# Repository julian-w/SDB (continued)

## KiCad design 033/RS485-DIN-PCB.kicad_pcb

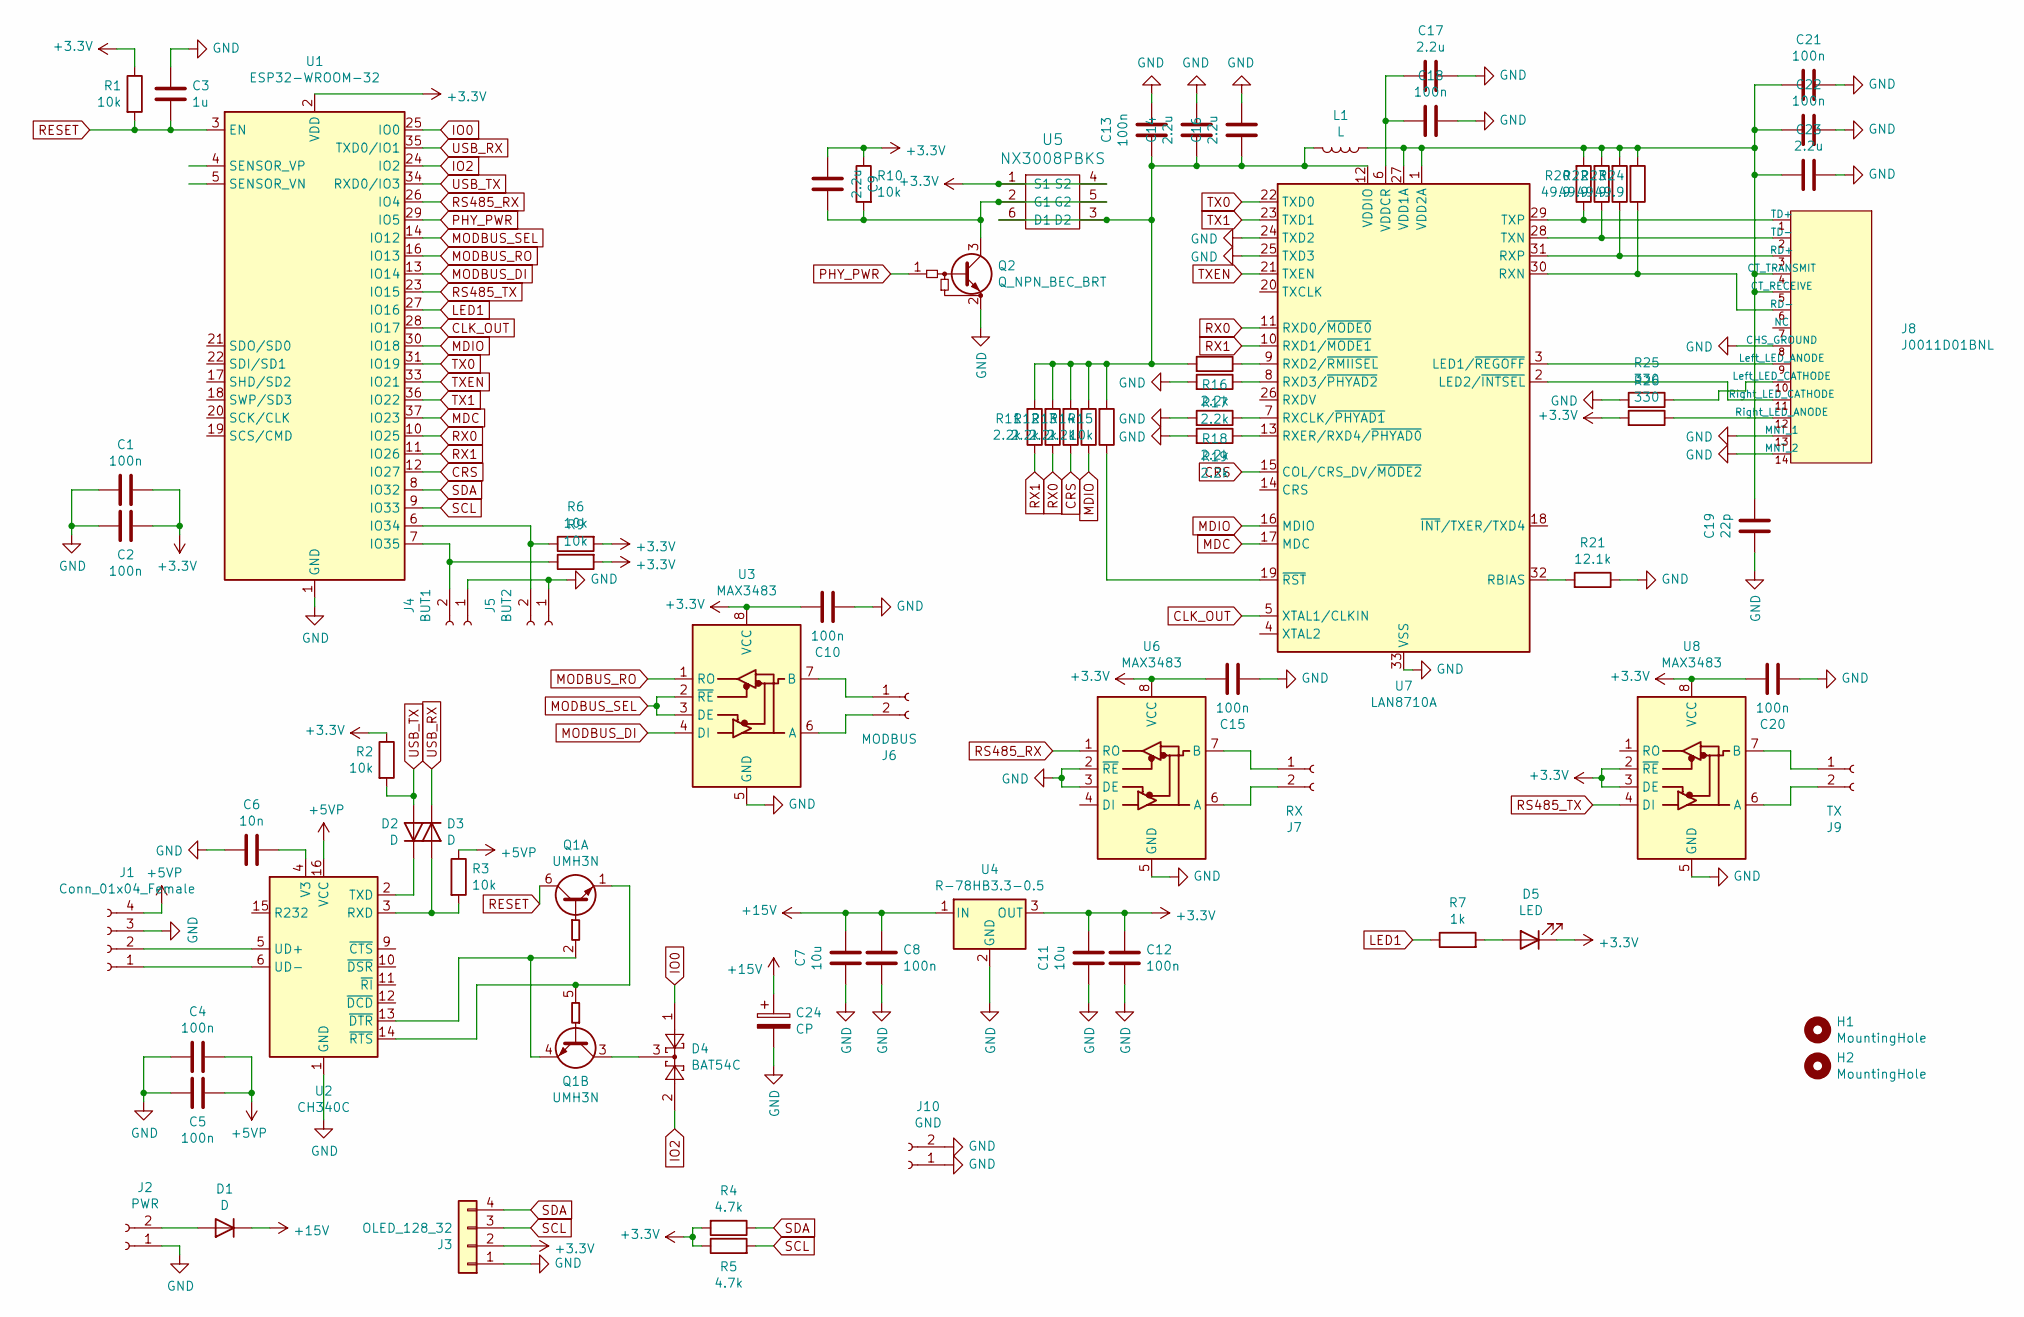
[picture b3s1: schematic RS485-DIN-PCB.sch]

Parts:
C1, C2, C4, C5, C10, C12, C13, C15, C18, C20, C21, C22: 100n; C_0603
C3: 1u; C_0603
C6: 10n; C_0603
C7: 10u; C_0805
C8: 100n; C_0805
C9, C14, C16, C17, C23: 2.2u; C_0603
C11: 10u; C_0603
C19: 22p; C_0603
C24: CP; CP_Radial_D8.0mm_P3.50mm
D1: D; D_SMA
D2, D3: D; D_SOD-123; LCSC C8598
D4: BAT54C; SOT-23
D5: LED; LED_D3.0mm_FlatTop
H1, H2: MountingHole; MountingHole_4.3mm_M4
J1: Conn_01x04_Female; PinHeader_1x04_P2.54mm_Vertical
J2: PWR; PinHeader_1x02_P2.54mm_Vertical
J3: OLED_128_32; SSD1306-0.91-OLED-4pin-128x32
J4: BUT1; PinHeader_1x02_P2.54mm_Vertical
J5: BUT2; PinHeader_1x02_P2.54mm_Vertical
J6: MODBUS; PinHeader_1x02_P2.54mm_Vertical
J7: RX; PinHeader_1x02_P2.54mm_Vertical
J8: J0011D01BNL; Pulse-J0011D01BNL-0-0-0; mouser part number 673-J0011D01BNL; digikey description CONN MAGJACK 1PORT 100 BASE-TX
J9: TX; PinHeader_1x02_P2.54mm_Vertical
J10: GND; PinHeader_1x02_P2.54mm_Vertical
L1: L; R_0603_HandSoldering
Q1: UMH3N; SOT-363_SC-70-6
Q2: Q_NPN_BEC_BRT; SOT-23
R1, R2, R3, R6, R9, R10, R15: 10k; R_0603
R4, R5: 4.7k; R_0603
R7: 1k; R_0603
R11, R12, R13, R14, R16, R17, R18, R19: 2.2k; R_0603
R20, R22, R23, R24: 49.9; R_0603
R21: 12.1k; R_0603
R25, R26: 330; R_0603
U1: ESP32-WROOM-32
U2: CH340C; SOIC-16_3.9x9.9mm_P1.27mm; LCSC C14267
U3, U6, U8: MAX3483; SOIC-8_3.9x4.9mm_P1.27mm
U4: R-78HB3.3-0.5; Converter_DCDC_RECOM_R-78HB-0.5_THT
U5: NX3008PBKS; TSOP-6_1.65x3.05mm_P0.95mm
U7: LAN8710A; QFN-32-1EP_5x5mm_P0.5mm_EP3.3x3.3mm_ThermalVias

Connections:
+3V3: C1.1, C2.1, C9.2, C10.1, C11.1, C12.1, C15.1, C20.1, D5.1 (K), J3.2, R1.1, R2.1, R4.2, R5.1, R6.2, R9.2, R10.1, R26.2, U1.2 (VDD), U3.8 (VCC), U4.3 (OUT), U5.1 (S1), U5.4 (S2), U6.8 (VCC), U8.2 (~RE), U8.3 (DE), U8.8 (VCC)
+5VP: C4.1, C5.1, J1.4, R3.1, U2.16 (VCC)
+15V: C7.1, C8.1, C24.1, D1.1 (K), U4.1 (IN)
CLK_OUT: U1.28 (IO17), U7.5 (XTAL1/CLKIN)
CRS: R13.1, U1.12 (IO27), U7.15 (COL/CRS_DV/~MODE2)
GND: C1.2, C2.2, C3.2, C4.2, C5.2, C6.2, C7.2, C8.2, C10.2, C11.2, C12.2, C13.1, C14.1, C15.2, C16.1, C17.1, C18.1, C19.2, C20.2, C21.1, C22.1, C23.1, C24.2, J1.3, J2.1, J3.1, J4.1, J5.1, J8.8 (CHS_GROUND), J8.13 (MNT_1), J8.14 (MNT_2), J10.1, J10.2, Q2.2 (E), R17.2, R18.2, R19.2, R21.1, R25.2, U1.1 (GND), U1.15 (GND), U1.38 (GND), U1.39 (GND), U2.1 (GND), U3.5 (GND), U4.2 (GND), U6.2 (~RE), U6.3 (DE), U6.5 (GND), U7.24 (TXD2), U7.25 (TXD3), U7.33 (VSS), U8.5 (GND)
IO0: D4.1, U1.25 (IO0)
IO2: D4.2, U1.24 (IO2)
LED1: R7.1, U1.27 (IO16)
MDC: U1.37 (IO23), U7.17 (MDC)
MDIO: R14.1, U1.30 (IO18), U7.16 (MDIO)
MODBUS_DI: U1.13 (IO14), U3.4 (DI)
MODBUS_RO: U1.16 (IO13), U3.1 (RO)
MODBUS_SEL: U1.14 (IO12), U3.2 (~RE), U3.3 (DE)
unnamed: C6.1, U2.4 (V3)
unnamed: C9.1, Q2.3 (C), R10.2, U5.2 (G1), U5.5 (G2)
unnamed: C13.2, C14.2, C16.2, L1.2, R11.2, R12.2, R13.2, R14.2, R15.2, R16.2, U5.3 (D2), U5.6 (D1), U7.12 (VDDIO)
unnamed: C17.2, C18.2, U7.6 (VDDCR)
unnamed: C19.1, C21.2, C22.2, C23.2, J8.4 (CT_TRANSMIT), J8.5 (CT_RECEIVE), L1.1, R20.2, R22.2, R23.2, R24.2, U7.1 (VDD2A), U7.27 (VDD1A)
unnamed: D1.2 (A), J2.2
unnamed: D2.1 (K), U2.2 (TXD)
unnamed: D3.2 (A), R3.2, U2.3 (RXD)
unnamed: D4.3, Q1.3 (C2)
unnamed: D5.2 (A), R7.2
unnamed: J1.1, U2.6 (UD-)
unnamed: J1.2, U2.5 (UD+)
unnamed: J4.2, R9.1, U1.7 (IO35)
unnamed: J5.2, R6.1, U1.6 (IO34)
unnamed: J6.1, U3.7 (B)
unnamed: J6.2, U3.6 (A)
unnamed: J7.1, U6.7 (B)
unnamed: J7.2, U6.6 (A)
unnamed: J8.1 (TD+), R20.1, U7.29 (TXP)
unnamed: J8.2 (TD-), R22.1, U7.28 (TXN)
unnamed: J8.3 (RD+), R23.1, U7.31 (RXP)
unnamed: J8.6 (RD-), R24.1, U7.30 (RXN)
unnamed: J8.9 (Left_LED_ANODE), U7.3 (LED1/~REGOFF)
unnamed: J8.10 (Left_LED_CATHODE), R25.1
unnamed: J8.11 (Right_LED_CATHODE), U7.2 (LED2/~INTSEL)
unnamed: J8.12 (Right_LED_ANODE), R26.1
unnamed: J9.1, U8.7 (B)
unnamed: J9.2, U8.6 (A)
unnamed: Q1.1 (E1), Q1.5 (B2), U2.14 (~RTS)
unnamed: Q1.2 (B1), Q1.4 (E2), U2.13 (~DTR)
unnamed: R15.1, U7.19 (~RST)
unnamed: R16.1, U7.9 (RXD2/~RMIISEL)
unnamed: R17.1, U7.8 (RXD3/~PHYAD2)
unnamed: R18.1, U7.7 (RXCLK/~PHYAD1)
unnamed: R19.1, U7.13 (RXER/RXD4/~PHYAD0)
unnamed: R21.2, U7.32 (RBIAS)
PHY_PWR: Q2.1 (B), U1.29 (IO5)
RESET: C3.1, Q1.6 (C1), R1.2, U1.3 (EN)
RS485_RX: U1.26 (IO4), U6.1 (RO)
RS485_TX: U1.23 (IO15), U8.4 (DI)
RX0: R12.1, U1.10 (IO25), U7.11 (RXD0/~MODE0)
RX1: R11.1, U1.11 (IO26), U7.10 (RXD1/~MODE1)
SCL: J3.3, R5.2, U1.9 (IO33)
SDA: J3.4, R4.1, U1.8 (IO32)
TX0: U1.31 (IO19), U7.22 (TXD0)
TX1: U1.36 (IO22), U7.23 (TXD1)
TXEN: U1.33 (IO21), U7.21 (TXEN)
USB_RX: D3.1 (K), U1.35 (TXD0/IO1)
USB_TX: D2.2 (A), R2.2, U1.34 (RXD0/IO3)

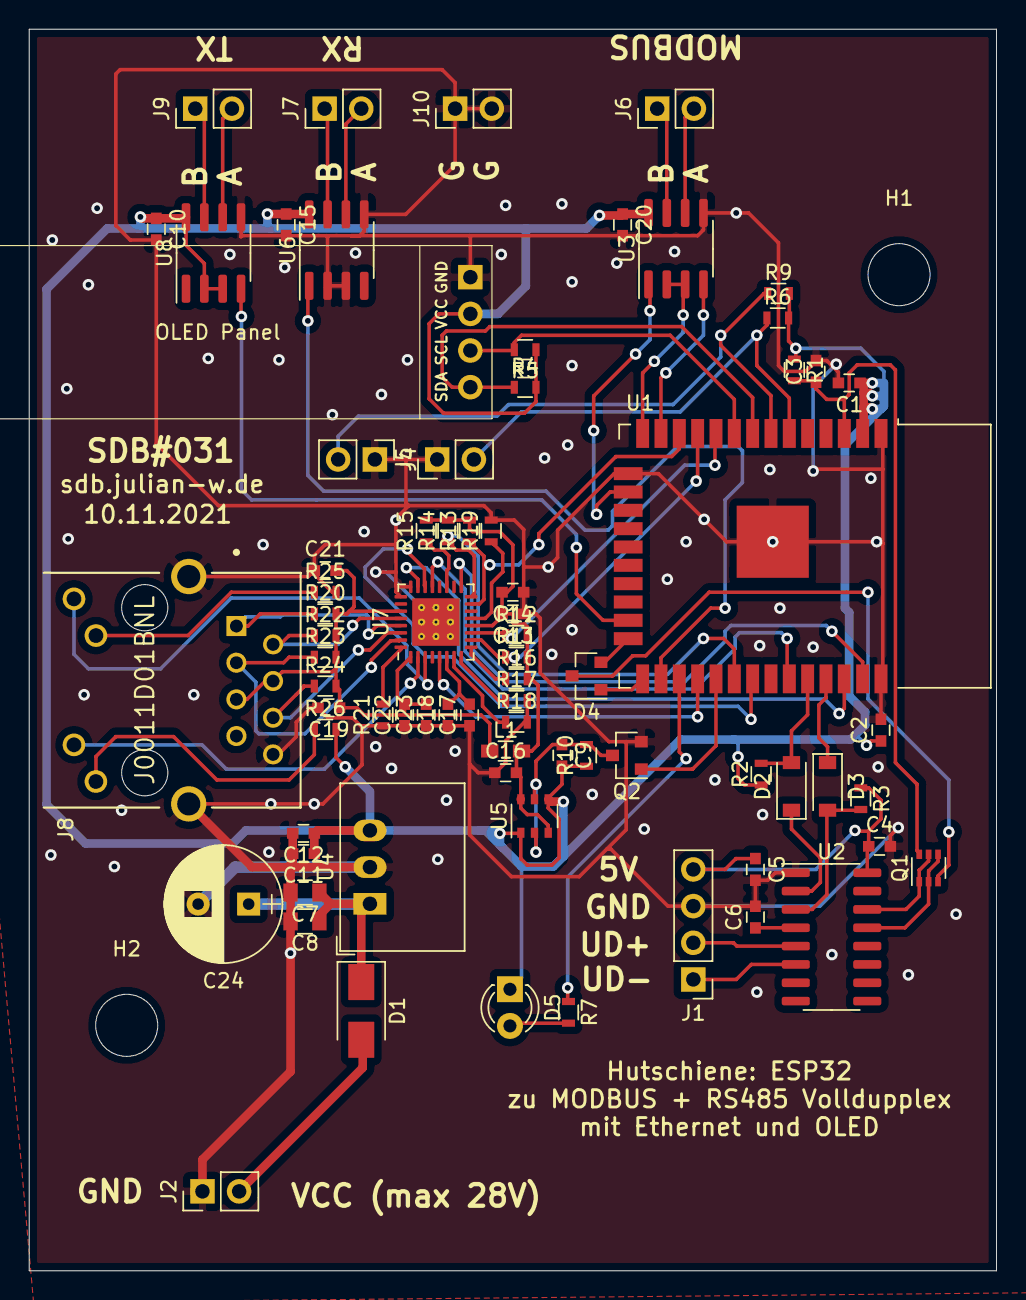
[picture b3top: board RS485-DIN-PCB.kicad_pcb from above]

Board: 2 copper layers, 67.0 x 86.0 mm, 77 parts (0 on the bottom side), 63 nets.

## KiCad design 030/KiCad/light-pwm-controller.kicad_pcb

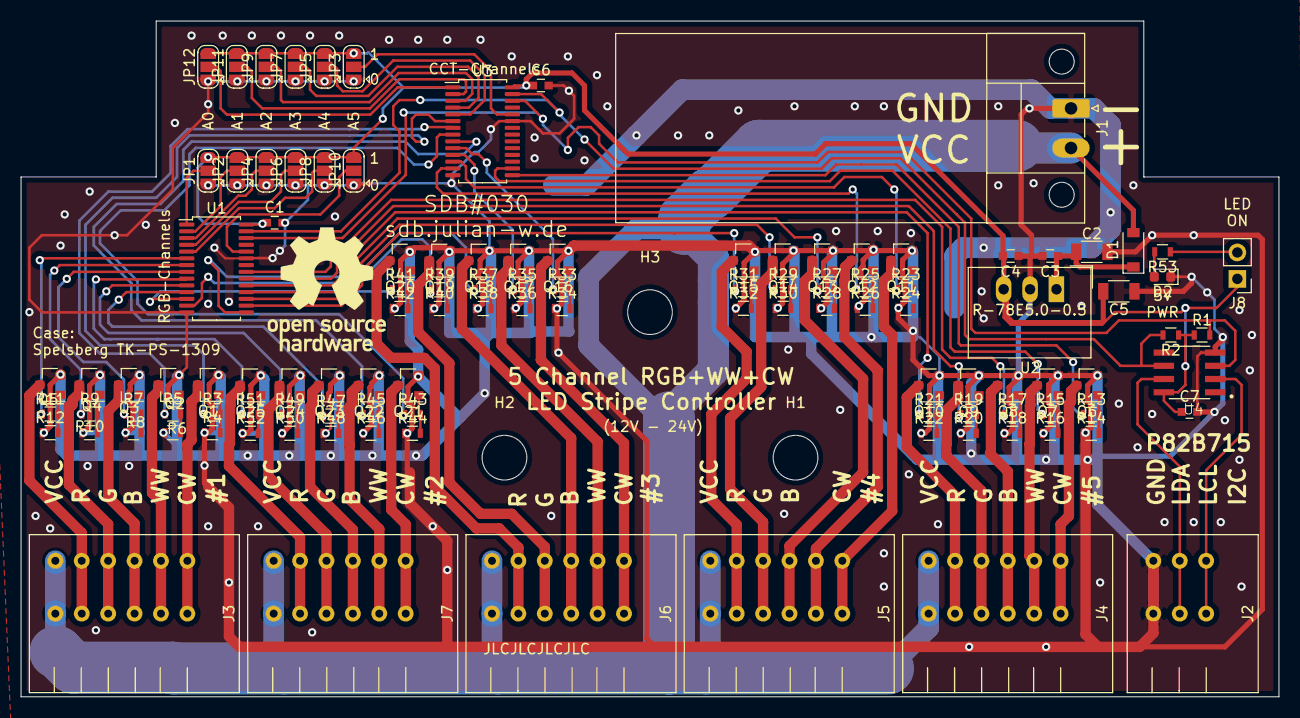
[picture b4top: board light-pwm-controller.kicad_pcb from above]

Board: 2 copper layers, 121.0 x 65.0 mm, 115 parts (0 on the bottom side), 97 nets.

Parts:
C1, C3, C4, C6, C7: 100n; C_0603
C2, C5: 10u; C_1206
D1: D; D_SOD-123
D2: LED; LED_0603_1608Metric
H1, H2, H3: MountingHole; MountingHole_4.3mm_M4
J1: Conn_01x02; PhoenixContact_MC_1,5_2-GF-3.81_1x02_P3.81mm_Horizontal_Thr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
J2: Conn_01x03; 3x2.54SpringClamp
J3, J4, J5, J6, J7: Conn_01x06; 6x2.54SpringClamp
J8: Conn_01x02; PinHeader_1x02_P2.54mm_Vertical
JP1, JP12: 1A0; SolderJumper-3_P1.3mm_Open_RoundedPad1.0x1.5mm
JP2, JP11: 1A1; SolderJumper-3_P1.3mm_Open_RoundedPad1.0x1.5mm
JP3, JP10: 1A5; SolderJumper-3_P1.3mm_Open_RoundedPad1.0x1.5mm
JP4, JP9: 1A2; SolderJumper-3_P1.3mm_Open_RoundedPad1.0x1.5mm
JP5, JP8: 1A4; SolderJumper-3_P1.3mm_Open_RoundedPad1.0x1.5mm
JP6, JP7: 1A3; SolderJumper-3_P1.3mm_Open_RoundedPad1.0x1.5mm
LOGO1: OSHW-LOGOM; OSHW-Logo_11.4x12mm_SilkScreen
Q1, Q2, Q3, Q4, Q5, Q6, Q7, Q8, Q9, Q10, Q11, Q12, Q13, Q14, Q15, Q16, Q17, Q18, Q19, Q20, Q21, Q22, Q23, Q24, Q25: IRLML6344; SOT-23
R1, R2: 4.7k; R_0603
R3, R5, R7, R9, R11, R13, R15, R17, R19, R21, R23, R25, R27, R29, R31, R33, R35, R37, R39, R41, R43, R45, R47, R49, R51: 100; R_0603
R4, R6, R8, R10, R12, R14, R16, R18, R20, R22, R24, R26, R28, R30, R32, R34, R36, R38, R40, R42, R44, R46, R48, R50, R52: 10k; R_0603
R53: 1k; R_0603
U1, U3: PCA9685PW; TSSOP-28_4.4x9.7mm_P0.65mm
U2: R-78E5.0-0.5; DCDC-Conv_RECOM_R-78E-0.5
U4: P82B715DR; SOIC127P599X175-8N

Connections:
+5V: C1.1, C4.2, C5.2, C6.1, C7.1, J8.1, JP1.3, JP2.3, JP3.3, JP4.3, JP5.3, JP6.3, JP7.3, JP8.3, JP9.3, JP10.3, JP11.3, JP12.3, R1.1, R2.1, U1.28, U2.3, U3.28, U4.8
+12V: D1.2, J1.2, J3.6, J4.6, J5.6, J6.6, J7.6
/output-stage-1/B: R7.1, U1.8
/output-stage-1/CW: R3.1, U3.6
/output-stage-1/G: R9.1, U1.7
/output-stage-1/R: R11.1, U1.6
/output-stage-1/WW: R5.1, U3.7
/output-stage-2/B: R17.1, U1.21
/output-stage-2/CW: R13.1, U3.15
/output-stage-2/G: R19.1, U1.20
/output-stage-2/R: R21.1, U1.19
/output-stage-2/WW: R15.1, U3.16
/output-stage-3/B: R27.1, U1.18
/output-stage-3/CW: R23.1, U3.12
/output-stage-3/G: R29.1, U1.17
/output-stage-3/R: R31.1, U1.16
/output-stage-3/WW: R25.1, U3.13
/output-stage-4/B: R37.1, U1.15
/output-stage-4/CW: R33.1, U3.10
/output-stage-4/G: R39.1, U1.13
/output-stage-4/R: R41.1, U1.12
/output-stage-4/WW: R35.1, U3.11
/output-stage-5/B: R47.1, U1.11
/output-stage-5/CW: R43.1, U3.8
/output-stage-5/G: R49.1, U1.10
/output-stage-5/R: R51.1, U1.9
/output-stage-5/WW: R45.1, U3.9
GND: C1.2, C2.2, C3.2, C4.1, C5.1, C6.2, C7.2, D2.1, J1.1, J2.3, JP1.1, JP2.1, JP3.1, JP4.1, JP5.1, JP6.1, JP7.1, JP8.1, JP9.1, JP10.1, JP11.1, JP12.1, Q1.2, Q2.2, Q3.2, Q4.2, Q5.2, Q6.2, Q7.2, Q8.2, Q9.2, Q10.2, Q11.2, Q12.2, Q13.2, Q14.2, Q15.2, Q16.2, Q17.2, Q18.2, Q19.2, Q20.2, Q21.2, Q22.2, Q23.2, Q24.2, Q25.2, R4.1, R6.1, R8.1, R10.1, R12.1, R14.1, R16.1, R18.1, R20.1, R22.1, R24.1, R26.1, R28.1, R30.1, R32.1, R34.1, R36.1, R38.1, R40.1, R42.1, R44.1, R46.1, R48.1, R50.1, R52.1, U1.14, U1.23, U2.2, U3.14, U3.23, U4.4
unnamed: C2.1, C3.1, D1.1, U2.1
unnamed: D2.2, R53.2
unnamed: J2.1, U4.2
unnamed: J2.2, U4.7
unnamed: J3.1, Q1.3
unnamed: J3.2, Q2.3
unnamed: J3.3, Q3.3
unnamed: J3.4, Q4.3
unnamed: J3.5, Q5.3
unnamed: J4.1, Q6.3
unnamed: J4.2, Q7.3
unnamed: J4.3, Q8.3
unnamed: J4.4, Q9.3
unnamed: J4.5, Q10.3
unnamed: J5.1, Q11.3
unnamed: J5.2, Q12.3
unnamed: J5.3, Q13.3
unnamed: J5.4, Q14.3
unnamed: J5.5, Q15.3
unnamed: J6.1, Q16.3
unnamed: J6.2, Q17.3
unnamed: J6.3, Q18.3
unnamed: J6.4, Q19.3
unnamed: J6.5, Q20.3
unnamed: J7.1, Q21.3
unnamed: J7.2, Q22.3
unnamed: J7.3, Q23.3
unnamed: J7.4, Q24.3
unnamed: J7.5, Q25.3
unnamed: J8.2, R53.1
unnamed: JP1.2, U1.1
unnamed: JP2.2, U1.2
unnamed: JP3.2, U3.24
unnamed: JP4.2, U1.3
unnamed: JP5.2, U3.5
unnamed: JP6.2, U1.4
unnamed: JP7.2, U3.4
unnamed: JP8.2, U1.5
unnamed: JP9.2, U3.3
unnamed: JP10.2, U1.24
unnamed: JP11.2, U3.2
unnamed: JP12.2, U3.1
unnamed: Q1.1, R3.2, R4.2
unnamed: Q2.1, R5.2, R6.2
unnamed: Q3.1, R7.2, R8.2
unnamed: Q4.1, R9.2, R10.2
unnamed: Q5.1, R11.2, R12.2
unnamed: Q6.1, R13.2, R14.2
unnamed: Q7.1, R15.2, R16.2
unnamed: Q8.1, R17.2, R18.2
unnamed: Q9.1, R19.2, R20.2
unnamed: Q10.1, R21.2, R22.2
unnamed: Q11.1, R23.2, R24.2
unnamed: Q12.1, R25.2, R26.2
unnamed: Q13.1, R27.2, R28.2
unnamed: Q14.1, R29.2, R30.2
unnamed: Q15.1, R31.2, R32.2
unnamed: Q16.1, R33.2, R34.2
unnamed: Q17.1, R35.2, R36.2
unnamed: Q18.1, R37.2, R38.2
unnamed: Q19.1, R39.2, R40.2
unnamed: Q20.1, R41.2, R42.2
unnamed: Q21.1, R43.2, R44.2
unnamed: Q22.1, R45.2, R46.2
unnamed: Q23.1, R47.2, R48.2
unnamed: Q24.1, R49.2, R50.2
unnamed: Q25.1, R51.2, R52.2
SCL: R1.2, U1.26, U3.26, U4.3
SDA: R2.2, U1.27, U3.27, U4.6

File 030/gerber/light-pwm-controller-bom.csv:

Comment,Designator,Footprint,LCSC
10u,"C2,C5",Capacitors_SMD:C_1206,C13585
100n,"C1,C3,C4,C6,C7",Capacitors_SMD:C_0603,C14663
D,D1,Diodes_SMD:D_SOD-123,C8598
LED,D2,LED_SMD:LED_0603_1608Metric,C2286
MountingHole,"H1,H2,H3",Mounting_Holes:MountingHole_4.3mm_M4,
Conn_01x02,J1,"Connector_Phoenix_MC:PhoenixContact_MC_1,5_2-GF-3.81_1x02_P3.81mm_Horizontal_ThreadedFlange_MountHole",
Conn_01x03,J2,P-250-402:3x2.54SpringClamp,
Conn_01x06,"J3,J4,J5,J6,J7",P-250-402:6x2.54SpringClamp,
Conn_01x02,J8,Connector_PinHeader_2.54mm:PinHeader_1x02_P2.54mm_Vertical,
1A0,"JP1,JP12",SolderJumper:SolderJumper-3_P1.3mm_Open_RoundedPad1.0x1.5mm,
1A5,"JP3,JP10",SolderJumper:SolderJumper-3_P1.3mm_Open_RoundedPad1.0x1.5mm,
1A1,"JP2,JP11",SolderJumper:SolderJumper-3_P1.3mm_Open_RoundedPad1.0x1.5mm,
1A2,"JP4,JP9",SolderJumper:SolderJumper-3_P1.3mm_Open_RoundedPad1.0x1.5mm,
1A3,"JP6,JP7",SolderJumper:SolderJumper-3_P1.3mm_Open_RoundedPad1.0x1.5mm,
1A4,"JP5,JP8",SolderJumper:SolderJumper-3_P1.3mm_Open_RoundedPad1.0x1.5mm,
OSHW-LOGOM,LOGO1,Symbols:OSHW-Logo_11.4x12mm_SilkScreen,
IRLML6344,"Q1,Q2,Q3,Q4,Q5,Q6,Q7,Q8,Q9,Q10,Q11,Q12,Q13,Q14,Q15,Q16,Q17,Q18,Q19,Q20,Q21,Q22,Q23,Q24,Q25",Package_TO_SOT_SMD:SOT-23,C53550
4.7k,"R1,R2",Resistors_SMD:R_0603,C23162
100,"R3,R5,R7,R9,R11,R13,R15,R17,R19,R21,R23,R25,R27,R29,R31,R33,R35,R37,R39,R41,R43,R45,R47,R49,R51",Resistors_SMD:R_0603,C22775
1k,R53,Resistors_SMD:R_0603,C21190
10k,"R4,R6,R8,R10,R12,R14,R16,R18,R20,R22,R24,R26,R28,R30,R32,R34,R36,R38,R40,R42,R44,R46,R48,R50,R52",Resistors_SMD:R_0603,C25804
PCA9685PW,"U1,U3",Package_SO:TSSOP-28_4.4x9.7mm_P0.65mm,
R-78E5.0-0.5,U2,Converters_DCDC_ACDC:DCDC-Conv_RECOM_R-78E-0.5,
P82B715DR,U4,footprints:SOIC127P599X175-8N,

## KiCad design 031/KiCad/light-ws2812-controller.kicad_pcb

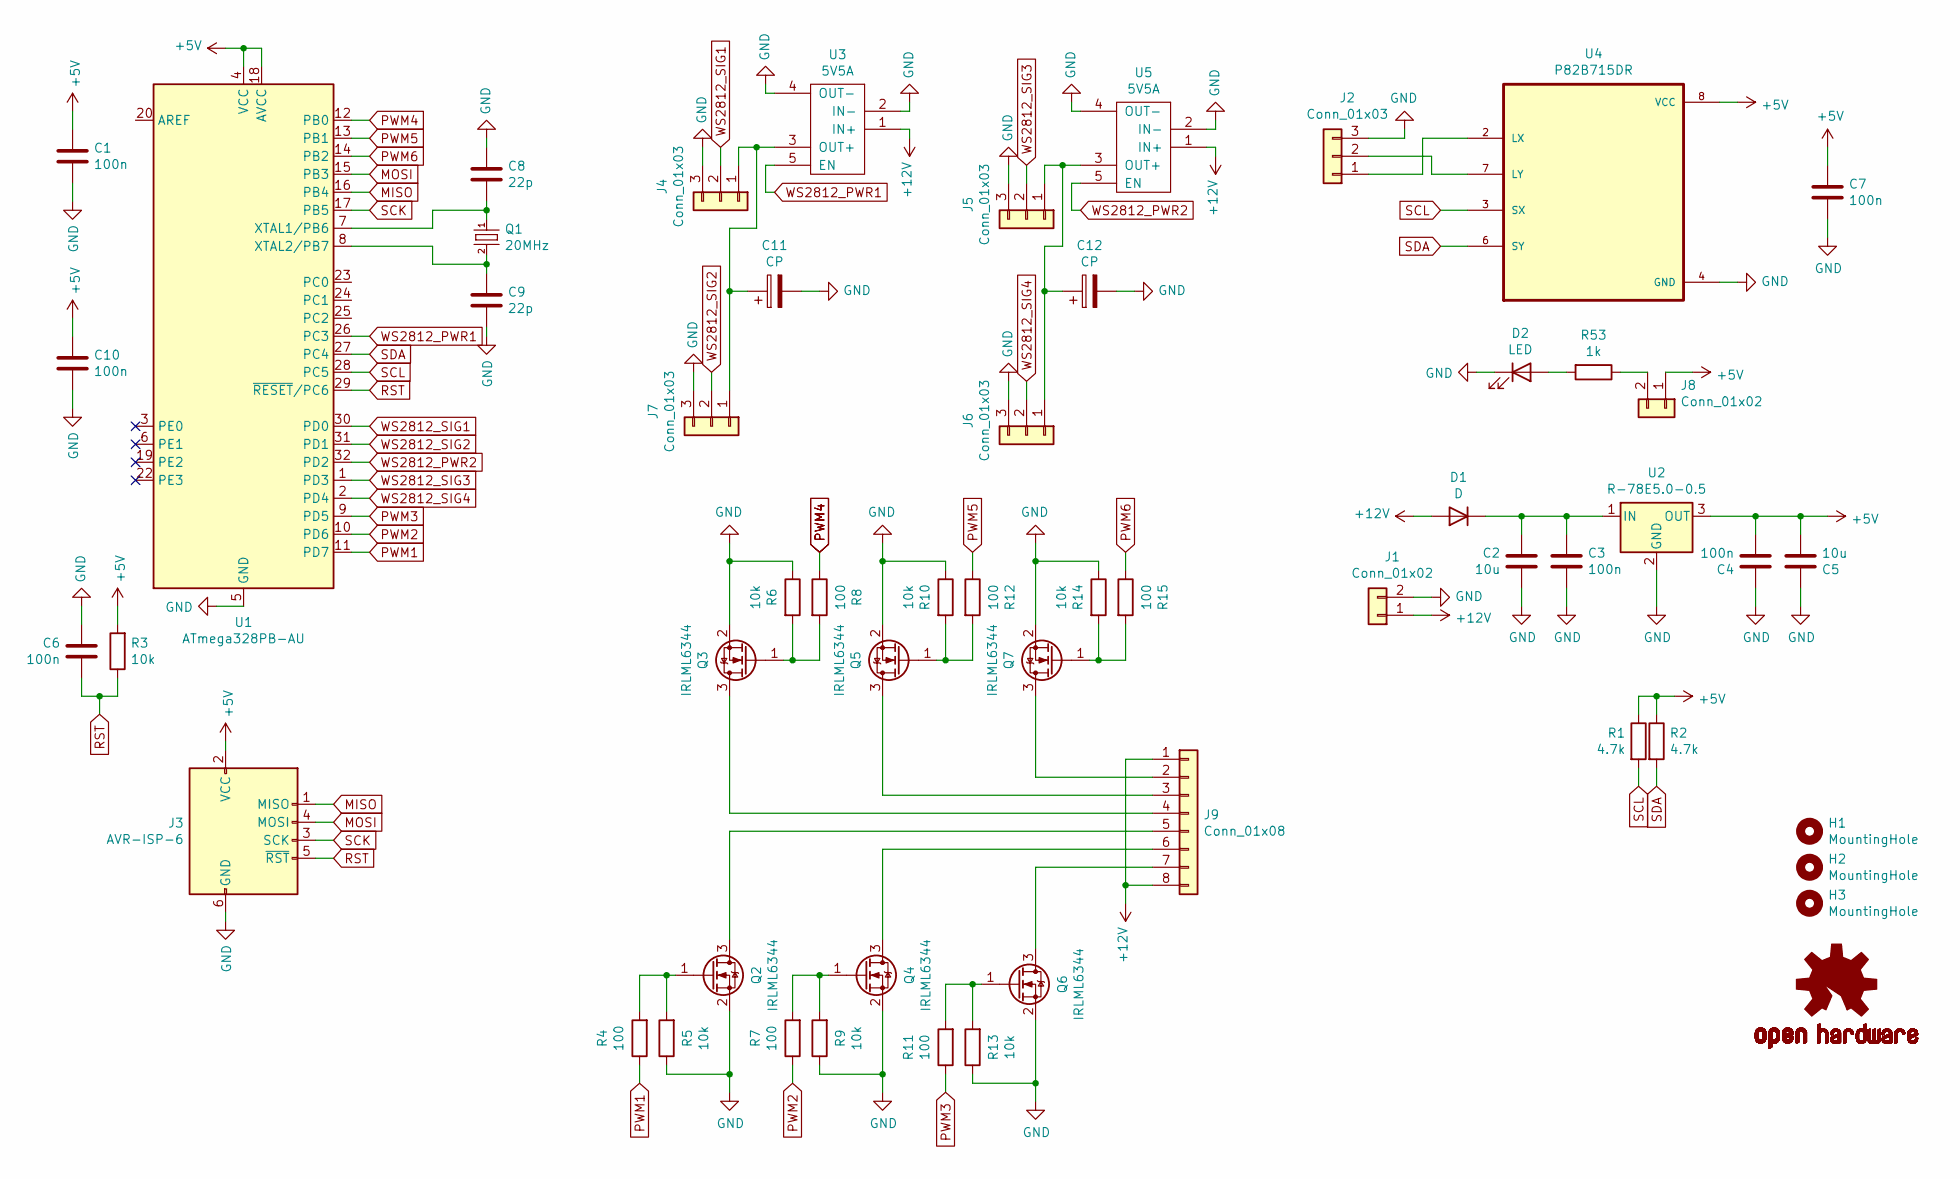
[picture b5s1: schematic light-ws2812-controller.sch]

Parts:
C1, C3, C4, C6, C7, C10: 100n; C_0603_HandSoldering
C2, C5: 10u; C_1206_HandSoldering
C8, C9: 22p; C_0603_HandSoldering
C11, C12: CP; CP_Radial_D10.0mm_P5.00mm_P7.50mm
D1: D; D_SOD-123
D2: LED; LED_0603_1608Metric
H1, H2, H3: MountingHole; MountingHole_4.3mm_M4
J1: Conn_01x02; PhoenixContact_MC_1,5_2-GF-3.81_1x02_P3.81mm_Horizontal_Thr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
J2, J4, J5, J6, J7: Conn_01x03; 3x2.54SpringClamp
J3: AVR-ISP-6; IDC-Header_2x03_P2.54mm_Vertical
J8: Conn_01x02; PinHeader_1x02_P2.54mm_Vertical
J9: Conn_01x08; 8x2.54SpringClamp
LOGO1: OSHW-LOGOM; OSHW-Logo_11.4x12mm_SilkScreen
Q1: 20MHz; Crystal_HC49-4H_Vertical
Q2, Q3, Q4, Q5, Q6, Q7: IRLML6344; SOT-23; LCSC C53550
R1, R2: 4.7k; R_0603_HandSoldering
R3, R5, R6, R9, R10, R13, R14: 10k; R_0603_HandSoldering
R4, R7, R8, R11, R12, R15: 100; R_0603_HandSoldering
R53: 1k; R_0603_HandSoldering
U1: ATmega328PB-AU; TQFP-32_7x7mm_P0.8mm
U2: R-78E5.0-0.5; DCDC-Conv_RECOM_R-78E-0.5
U3, U5: 5V5A
U4: P82B715DR; SOIC127P599X175-8N

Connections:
+5V: C1.1, C4.2, C5.2, C7.1, C10.1, J3.2 (VCC), J8.1, R1.1, R2.1, R3.2, U1.4 (VCC), U1.18 (AVCC), U2.3 (OUT), U4.8 (VCC)
+12V: D1.2 (A), J1.1, J9.1, J9.8, U3.1 (IN+), U5.1 (IN+)
GND: C1.2, C2.2, C3.2, C4.1, C5.1, C6.2, C7.2, C8.1, C9.2, C10.2, C11.2, C12.2, D2.1 (K), J1.2, J2.3, J3.6 (GND), J4.3, J5.3, J6.3, J7.3, Q2.2 (S), Q3.2 (S), Q4.2 (S), Q5.2 (S), Q6.2 (S), Q7.2 (S), R5.1, R6.1, R9.1, R10.1, R13.1, R14.1, U1.5 (GND), U1.21 (GND), U2.2 (GND), U3.2 (IN-), U3.4 (OUT-), U4.4 (GND), U5.2 (IN-), U5.4 (OUT-)
MISO: J3.1 (MISO), U1.16 (PB4)
MOSI: J3.4 (MOSI), U1.15 (PB3)
unnamed: C2.1, C3.1, D1.1 (K), U2.1 (IN)
unnamed: C8.2, Q1.1, U1.7 (XTAL1/PB6)
unnamed: C9.1, Q1.2, U1.8 (XTAL2/PB7)
unnamed: C11.1, J4.1, J7.1, U3.3 (OUT+)
unnamed: C12.1, J5.1, J6.1, U5.3 (OUT+)
unnamed: D2.2 (A), R53.2
unnamed: J2.1, U4.2 (LX)
unnamed: J2.2, U4.7 (LY)
unnamed: J8.2, R53.1
unnamed: J9.2, Q7.3 (D)
unnamed: J9.3, Q5.3 (D)
unnamed: J9.4, Q3.3 (D)
unnamed: J9.5, Q2.3 (D)
unnamed: J9.6, Q4.3 (D)
unnamed: J9.7, Q6.3 (D)
unnamed: Q2.1 (G), R4.2, R5.2
unnamed: Q3.1 (G), R6.2, R8.2
unnamed: Q4.1 (G), R7.2, R9.2
unnamed: Q5.1 (G), R10.2, R12.2
unnamed: Q6.1 (G), R11.2, R13.2
unnamed: Q7.1 (G), R14.2, R15.2
PWM1: R4.1, U1.11 (PD7)
PWM2: R7.1, U1.10 (PD6)
PWM3: R11.1, U1.9 (PD5)
PWM4: R8.1, U1.12 (PB0)
PWM5: R12.1, U1.13 (PB1)
PWM6: R15.1, U1.14 (PB2)
RST: C6.1, J3.5 (~RST), R3.1, U1.29 (~RESET~/PC6)
SCK: J3.3 (SCK), U1.17 (PB5)
SCL: R1.2, U1.28 (PC5), U4.3 (SX)
SDA: R2.2, U1.27 (PC4), U4.6 (SY)
WS2812_PWR1: U1.26 (PC3), U3.5 (EN)
WS2812_PWR2: U1.32 (PD2), U5.5 (EN)
WS2812_SIG1: J4.2, U1.30 (PD0)
WS2812_SIG2: J7.2, U1.31 (PD1)
WS2812_SIG3: J5.2, U1.1 (PD3)
WS2812_SIG4: J6.2, U1.2 (PD4)

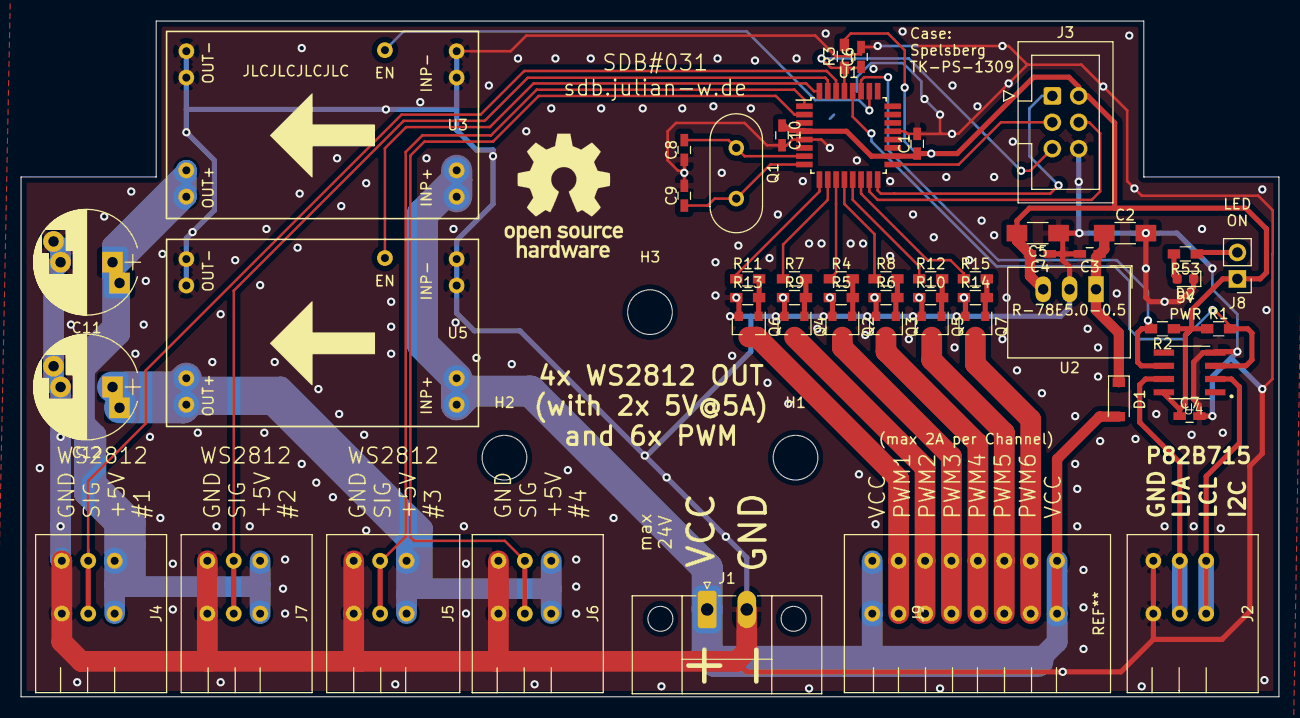
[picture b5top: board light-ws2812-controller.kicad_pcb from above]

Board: 2 copper layers, 121.0 x 65.0 mm, 55 parts (0 on the bottom side), 42 nets.

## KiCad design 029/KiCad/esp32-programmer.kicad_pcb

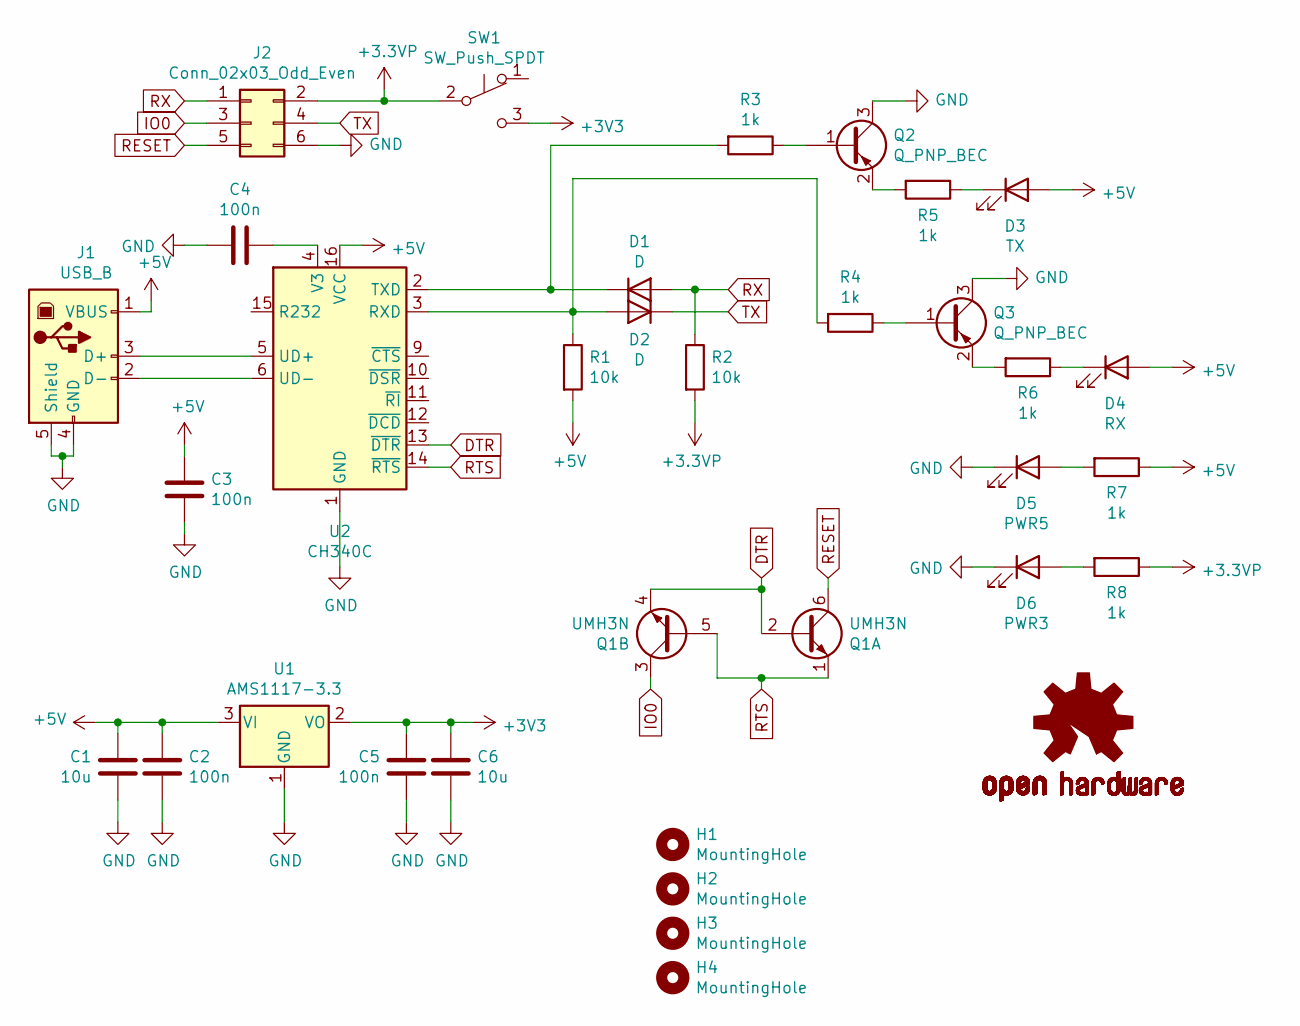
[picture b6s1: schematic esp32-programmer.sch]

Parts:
C1, C6: 10u; C_1206
C2, C3, C4, C5: 100n; C_0603
D1, D2: D; D_SOD-123
D3: TX; LED_0603_1608Metric
D4: RX; LED_0603_1608Metric
D5: PWR5; LED_0603_1608Metric
D6: PWR3; LED_0603_1608Metric
H1, H2, H3, H4: MountingHole; MountingHole_3.2mm_M3
J1: USB_B; USB_B_OST_USB-B1HSxx_Horizontal
J2: Conn_02x03_Odd_Even; IDC-Header_2x03_P2.54mm_Vertical
LOGO1: OSHW-LOGOL; OSHW-Logo_11.4x12mm_SilkScreen
Q1: UMH3N; SOT-363_SC-70-6
Q2, Q3: Q_PNP_BEC; SOT-23
R1, R2: 10k; R_0603
R3, R4, R5, R6, R7, R8: 1k; R_0603
SW1: SW_Push_SPDT; SW_Slide_1P2T_CK_OS102011MS2Q
U1: AMS1117-3.3; SOT-223-3_TabPin2
U2: CH340C; SOIC-16_3.9x9.9mm_P1.27mm

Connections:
+3.3VP: J2.2, R2.2, R8.1, SW1.2 (B)
+3V3: C5.1, C6.1, SW1.3 (C), U1.2 (VO)
+5V: C1.1, C2.1, C3.1, D3.2 (A), D4.2 (A), J1.1 (VBUS), R1.2, R7.1, U1.3 (VI), U2.16 (VCC)
DTR: Q1.2 (B1), Q1.4 (E2), U2.13 (~DTR)
GND: C1.2, C2.2, C3.2, C4.2, C5.2, C6.2, D5.1 (K), D6.1 (K), J1.4 (GND), J1.5 (Shield), J2.6, Q2.3 (C), Q3.3 (C), U1.1 (GND), U2.1 (GND)
IO0: J2.3, Q1.3 (C2)
unnamed: C4.1, U2.4 (V3)
unnamed: D1.1 (K), R3.2, U2.2 (TXD)
unnamed: D2.2 (A), R1.1, R4.2, U2.3 (RXD)
unnamed: D3.1 (K), R5.1
unnamed: D4.1 (K), R6.1
unnamed: D5.2 (A), R7.2
unnamed: D6.2 (A), R8.2
unnamed: J1.2 (D-), U2.6 (UD-)
unnamed: J1.3 (D+), U2.5 (UD+)
unnamed: Q2.1 (B), R3.1
unnamed: Q2.2 (E), R5.2
unnamed: Q3.1 (B), R4.1
unnamed: Q3.2 (E), R6.2
RESET: J2.5, Q1.6 (C1)
RTS: Q1.1 (E1), Q1.5 (B2), U2.14 (~RTS)
RX: D1.2 (A), J2.1, R2.1
TX: D2.1 (K), J2.4

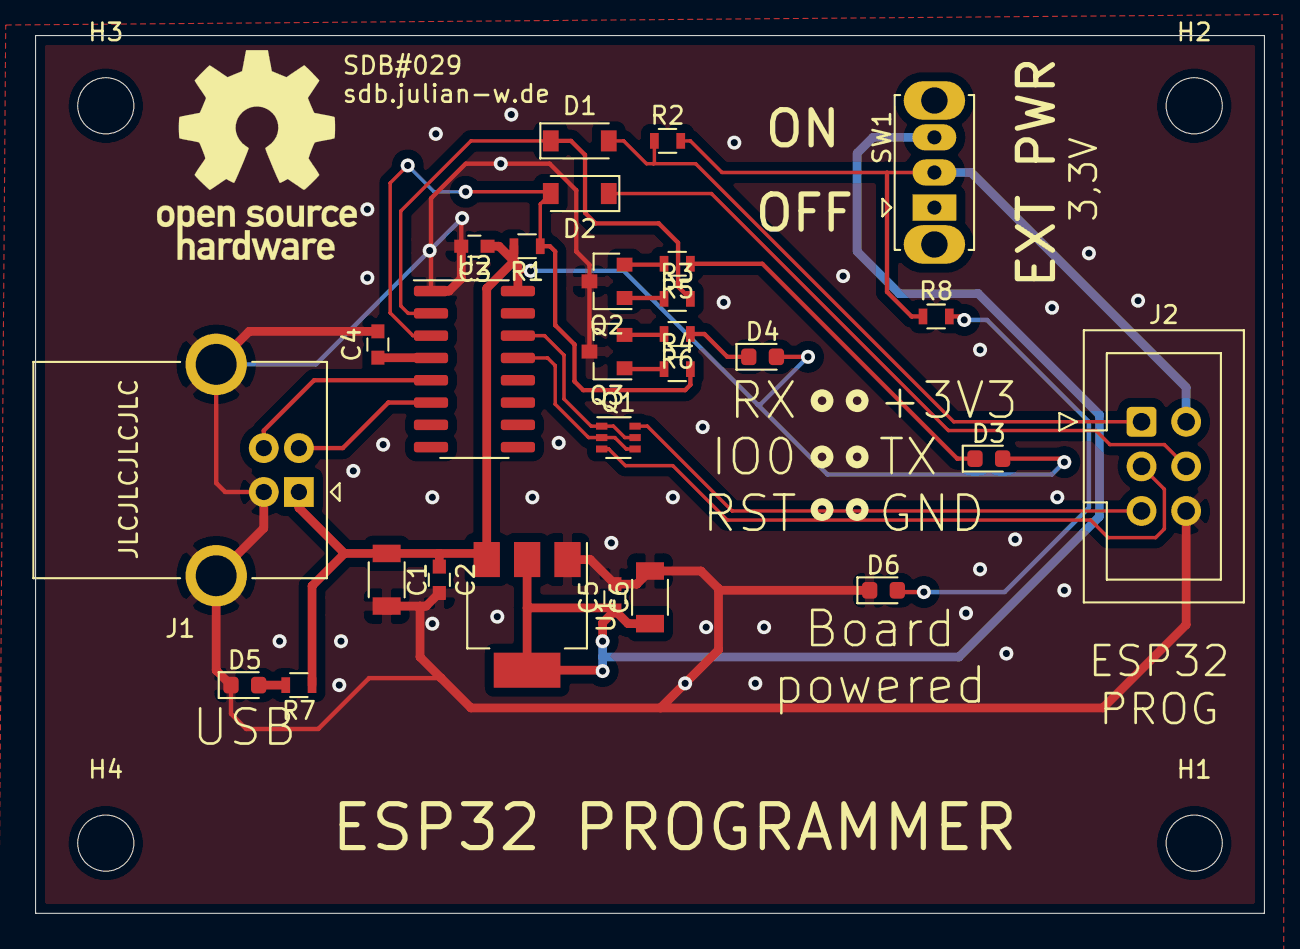
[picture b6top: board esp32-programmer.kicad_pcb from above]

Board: 2 copper layers, 70.0 x 50.0 mm, 33 parts (0 on the bottom side), 23 nets.

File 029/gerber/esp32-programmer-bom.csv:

Comment,Designator,Footprint,LCSC
100n,"C2,C3,C4,C5",Capacitors_SMD:C_0603,C14663
10u,"C1,C6",Capacitors_SMD:C_1206,C13585
D,"D1,D2",Diodes_SMD:D_SOD-123,C81598
TX,D3,LED_SMD:LED_0603_1608Metric,C72038
RX,D4,LED_SMD:LED_0603_1608Metric,C72043
PWR5,D5,LED_SMD:LED_0603_1608Metric,C2286
PWR3,D6,LED_SMD:LED_0603_1608Metric,C2286
MountingHole,"H1,H2,H3,H4",Mounting_Holes:MountingHole_3.2mm_M3,
USB_B,J1,Connector_USB:USB_B_OST_USB-B1HSxx_Horizontal,
Conn_02x03_Odd_Even,J2,Connector_IDC:IDC-Header_2x03_P2.54mm_Vertical,
PUMX1,Q1,Package_TO_SOT_SMD:SOT-363_SC-70-6,C79972
Q_PNP_BEC,"Q2,Q3",Package_TO_SOT_SMD:SOT-23,C8326
10k,"R1,R2",Resistors_SMD:R_0603,C25804 
1k,"R3,R4,R5,R6,R7,R8",Resistors_SMD:R_0603,C21190
SW_Push_SPDT,SW1,Button_Switch_THT:SW_Slide_1P2T_CK_OS102011MS2Q,
AMS1117-3.3,U1,Package_TO_SOT_SMD:SOT-223-3_TabPin2,C6186
CH340C,U2,Package_SO:SOIC-16_3.9x9.9mm_P1.27mm,C84681
